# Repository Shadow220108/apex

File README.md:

<h1 align="center">
  <br>

  <br>
  Apex
  <br>
</h1>
<h3 align="center">
A fully open-sourced compact devboard inspired by the Seed Studio Xiao RP2040 with extra features such as LiPo support 
</h3>

| Front Render | Back Render | 
| --- | --- |
|  |  | 

| Zine |
| --- |
|  |

## Features
- **RP2040 MCU** - Dual ARM Cortex-M0+ @ 133MHz MCU.
- **Very compact, XIAO SEEED inspired formfactor**.
- **4 ADC and 7 digital GPIO pins**.
- **5V and 3.3V power pins**.
- Power indicator LED, addressable LED and another RGB LED
- LiPo Battery support and charging circuit
- **USB C** - for programming and power.

## PCB Design 
| .jpg) |
|--- |  

 ### The PCB is 4 layers with dimensions 21x17.8mm, made to be easily replacable to any Xiao board.  

 ### All the PCB files are [here](https://github.com/Shadow220108/apex/blob/main/PCB) 

| Front Layer | Inner Layer 1 |
| --- | --- |
| .jpg) | .jpg) |
| Inner Layer 2 | Bottom layer |
| .jpg) | .jpg) |

## Schematics  

Here are the schematic designs,

|  |
| --- |  

## Pinout  

This is a general pinout 

|  | 
| --- | 

( Credits to the Seed Studio for making this, since my board is inspired on the Xiao, I have used the pinout provided by them ) 

## Why was it made?  

While using the Seed Studio Xiao RP2040 for one of my projects, I realised it doesn't have LiPo support   
and I couldn't use it, unfortunately I had to use a different MCU then, but now I designed one with  
the simplicity of RP2040 with being able to charge LiPo 

## How you can get one for yourself? 

That is pretty easy, you have all the files you will need in the production folder, order the development  
board from any PCB fab ( I chose JLC cause its cheap and has good quality ) and BINGO! You will have it  
to use for any purpose you want!  

## How do you use it?  
You can use it as any normal RP2040 Devboard, enter the boootloader mode  
by holding the BOOT buttom while connecting to your device, flash it with  
firmware and you are good to go!  I have attached a simple code to blink the LED  
available on the board.  

## BOM  
|Name|Purpose          |Quantity|Total Cost (USD)|Link               |Distributor|
|----|-----------------|--------|----------------|-------------------|-----------|
|PCBA|Development Board|2       |79.03           |https://jlcpcb.com/|JLCPCB     |
| | | Total | 79.03 | 

LCSC BOM for the components on board is [here](https://github.com/Shadow220108/apex/blob/main/production/apex_bom.csv)

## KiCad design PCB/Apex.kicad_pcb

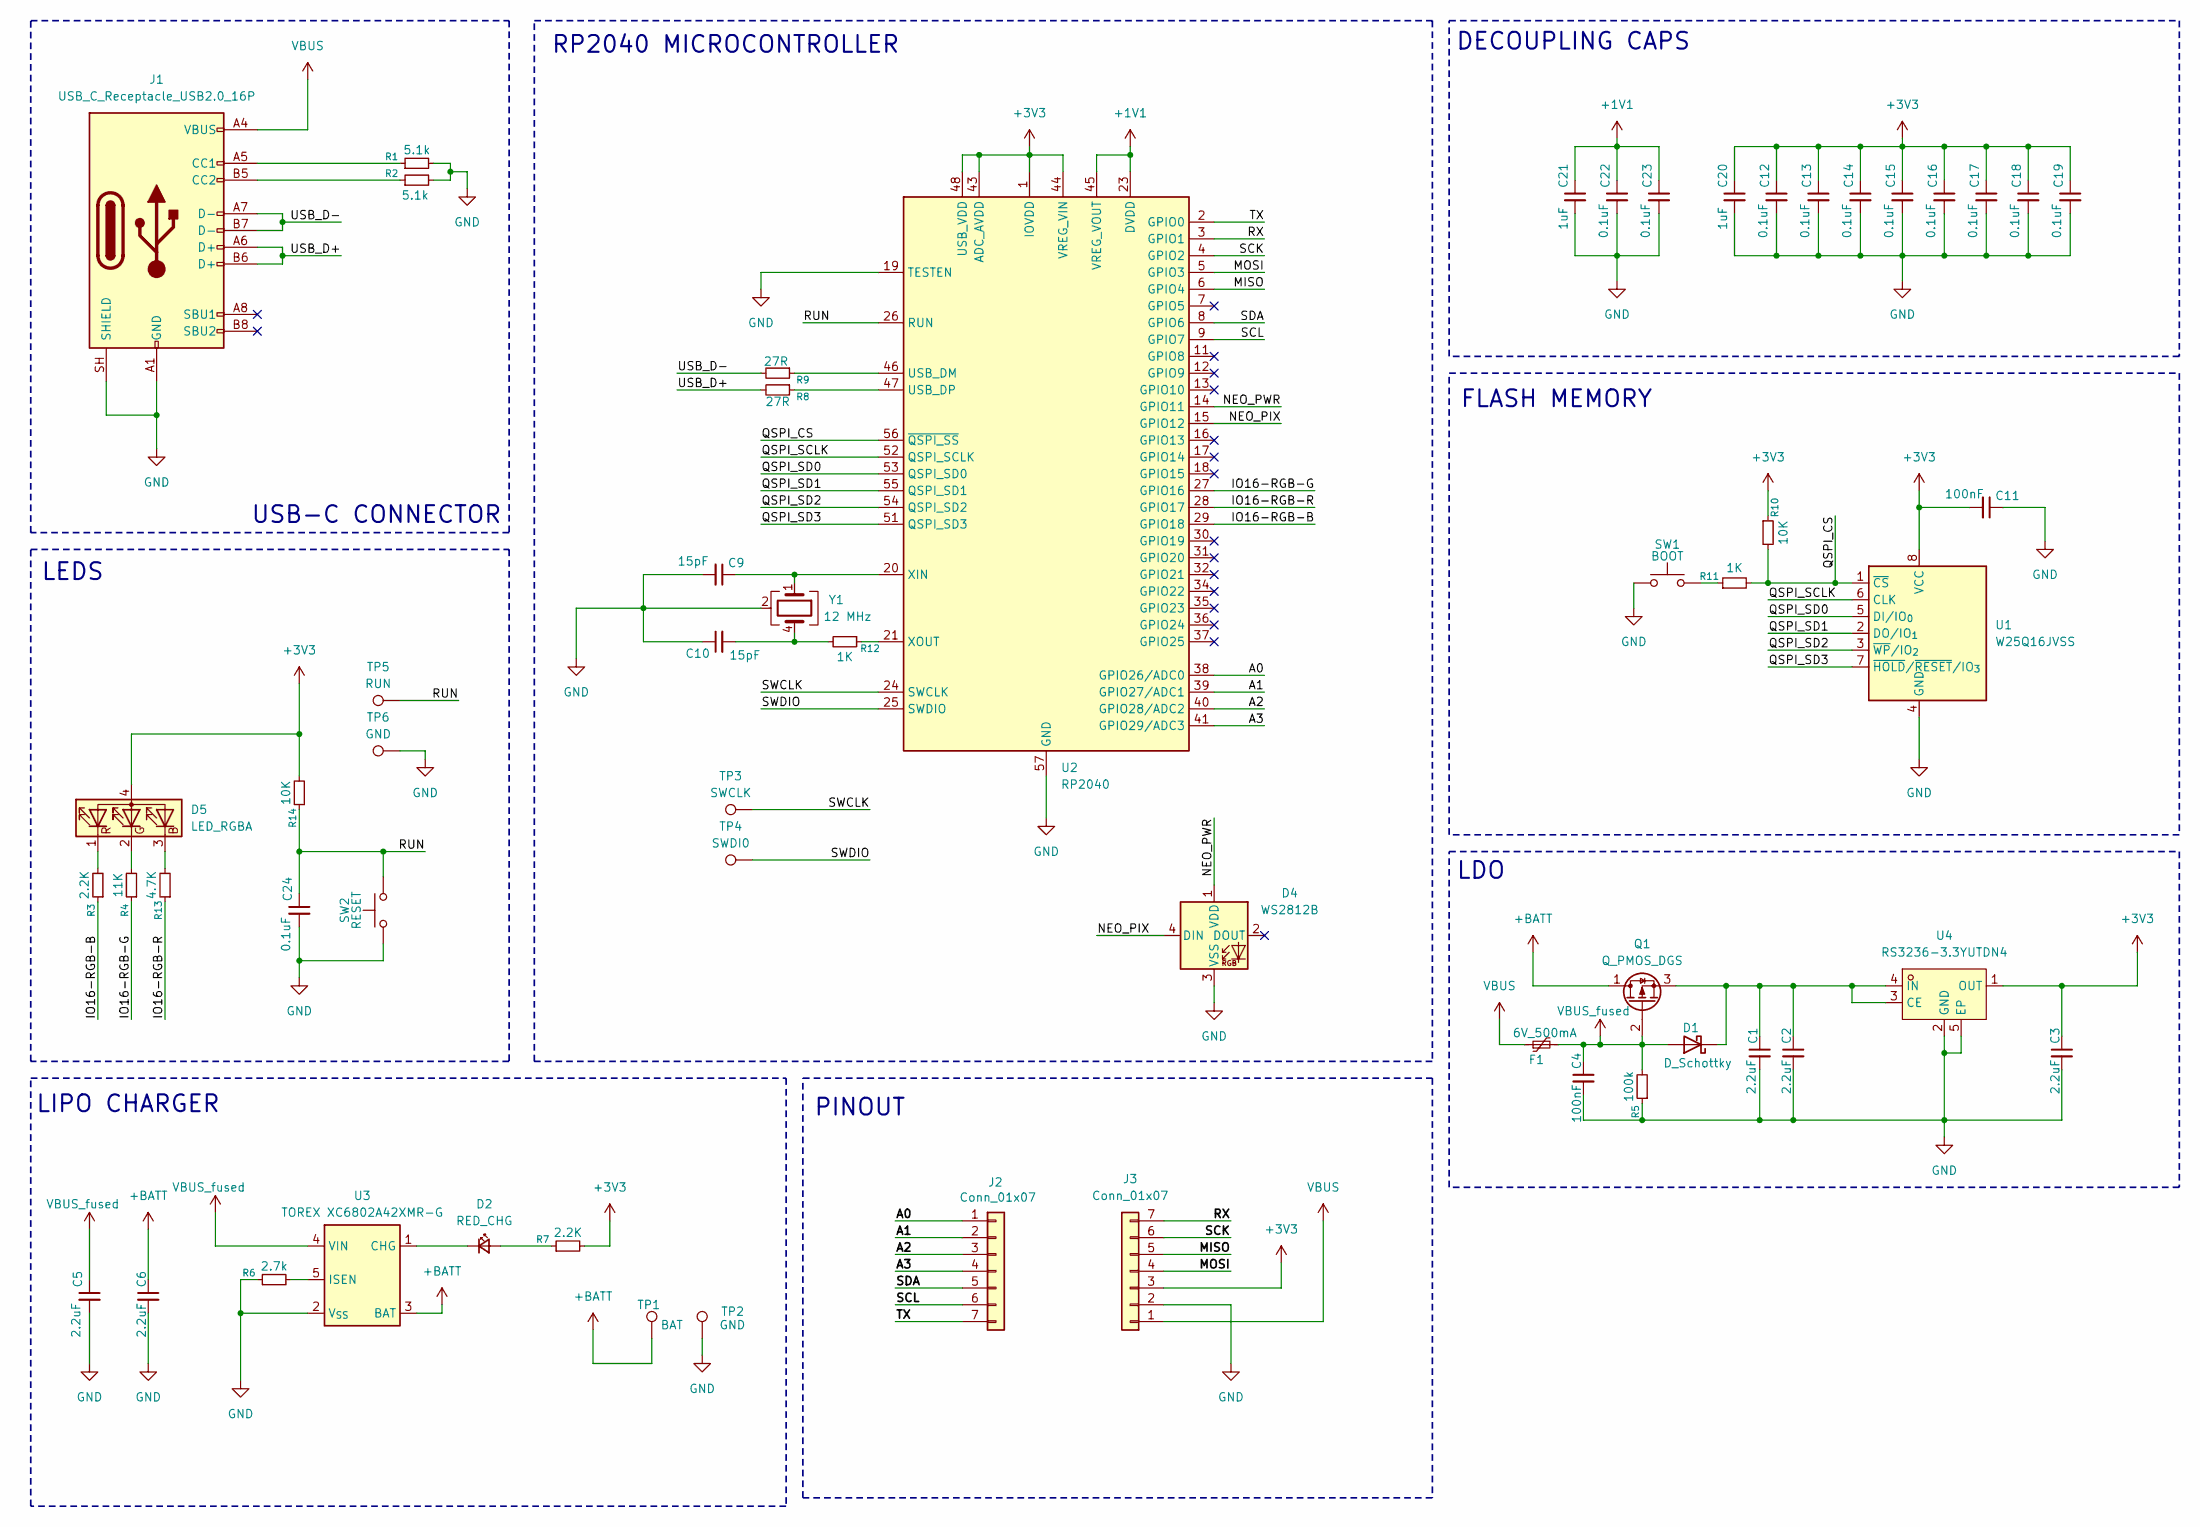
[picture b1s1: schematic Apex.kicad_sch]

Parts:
C1, C2, C3, C5, C6: 2.2uF; C_0201_0603Metric
C4, C11: 100nF; C_0201_0603Metric
C9, C10: 15pF; C_0201_0603Metric
C12, C13, C14, C15, C16, C17, C18, C19, C22, C23, C24: 0.1uF; C_0201_0603Metric
C20, C21: 1uF; C_0201_0603Metric
D1: D_Schottky; D_SOD-523
D2: RED_CHG; LED_0603_1608Metric
D4: WS2812B; LED_SK6805_PLCC4_2.4x2.7mm_P1.3mm
D5: LED_RGBA; LED_SK6812_EC15_1.5x1.5mm
F1: 6V_500mA; Fuse_0402_1005Metric
J1: USB_C_Receptacle_USB2.0_16P; USB-C_SMD-TYPE-C-31-M-12_1
J2, J3: Conn_01x07; PinHeader_1x07_P2.54mm_Vertical
Q1: Q_PMOS_DGS; SOT-323_SC-70
R1, R2: 5.1k; R_0201_0603Metric
R3, R7: 2.2K; R_0201_0603Metric
R4: 11K; R_0201_0603Metric
R5: 100k; R_0201_0603Metric
R6: 2.7k; R_0201_0603Metric
R8, R9: 27R; R_0201_0603Metric
R10, R14: 10K; R_0201_0603Metric
R11, R12: 1K; R_0201_0603Metric
R13: 4.7K; R_0201_0603Metric
SW1: BOOT; KEY-SMD_L3.0-W2.5-LS4.0_TD-1183SN
SW2: RESET; KEY-SMD_L3.0-W2.5-LS4.0_TD-1183SN
TP1: BAT; TestPoint_Pad_D1.0mm
TP2, TP6: GND; TestPoint_Pad_D1.0mm
TP3: SWCLK; TestPoint_Pad_D1.0mm
TP4: SWDI0; TestPoint_Pad_D1.0mm
TP5: RUN; TestPoint_Pad_D1.0mm
U1: W25Q16JVSS; USON-8_L3.0-W2.0-P0.50-BL-EP-1
U2: RP2040; QFN-56-1EP_7x7mm_P0.4mm_EP3.2x3.2mm
U3: TOREX XC6802A42XMR-G; SOT-23-5
U4: RS3236-3.3YUTDN4; XDFN-4_L1.0-W1.0-P0.65-BL-EP; MPN RS3236-3.3YUTDN4; LCSC Part C379350
Y1: 12 MHz; Crystal_SMD_1210-4Pin_1.2x1.0mm

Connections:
+1V1: C21.1, C22.1, C23.1, U2.23 (DVDD), U2.45 (VREG_VOUT), U2.50 (DVDD)
+3V3: C3.1, C11.2, C12.1, C13.1, C14.1, C15.1, C16.1, C17.1, C18.1, C19.1, C20.1, D5.4 (A), J3.3, R7.2, R10.1, R14.2, U1.8 (VCC), U2.1 (IOVDD), U2.10 (IOVDD), U2.22 (IOVDD), U2.33 (IOVDD), U2.42 (IOVDD), U2.43 (ADC_AVDD), U2.44 (VREG_VIN), U2.48 (USB_VDD), U2.49 (IOVDD), U4.1 (OUT)
+BATT: C6.1, Q1.1 (D), TP1.1 (1_1), U3.3 (BAT)
/A0: J2.1, U2.38 (GPIO26/ADC0)
/A1: J2.2, U2.39 (GPIO27/ADC1)
/A2: J2.3, U2.40 (GPIO28/ADC2)
/A3: J2.4, U2.41 (GPIO29/ADC3)
/IO16-RGB-B: R3.1, U2.29 (GPIO18)
/IO16-RGB-G: R4.1, U2.27 (GPIO16)
/IO16-RGB-R: R13.1, U2.28 (GPIO17)
/MISO: J3.5, U2.6 (GPIO4)
/MOSI: J3.4, U2.5 (GPIO3)
/NEO_PIX: D4.4 (DIN), U2.15 (GPIO12)
/NEO_PWR: D4.1 (VDD), U2.14 (GPIO11)
/QSPI_CS: R10.2, R11.2, U1.1 (~CS), U2.56 (~QSPI_SS)
/QSPI_SCLK: U1.6 (CLK), U2.52 (QSPI_SCLK)
/QSPI_SD0: U1.5 (DI/IO_{0}), U2.53 (QSPI_SD0)
/QSPI_SD1: U1.2 (DO/IO_{1}), U2.55 (QSPI_SD1)
/QSPI_SD2: U1.3 (~WP/IO_{2}), U2.54 (QSPI_SD2)
/QSPI_SD3: U1.7 (~HOLD/~RESET/IO_{3}), U2.51 (QSPI_SD3)
/RUN: C24.1, R14.1, SW2.2, TP5.1 (1_1), U2.26 (RUN)
/RX: J3.7, U2.3 (GPIO1)
/SCK: J3.6, U2.4 (GPIO2)
/SCL: J2.6, U2.9 (GPIO7)
/SDA: J2.5, U2.8 (GPIO6)
/SWCLK: TP3.1 (1_1), U2.24 (SWCLK)
/SWDIO: TP4.1 (1_1), U2.25 (SWDIO)
/TX: J2.7, U2.2 (GPIO0)
/USB_D+: J1.A6 (D+), J1.B6 (D+), R8.2
/USB_D-: J1.A7 (D-), J1.B7 (D-), R9.2
GND: C1.2, C2.2, C3.2, C4.2, C5.2, C6.2, C9.2, C10.1, C11.1, C12.2, C13.2, C14.2, C15.2, C16.2, C17.2, C18.2, C19.2, C20.2, C21.2, C22.2, C23.2, C24.2, D4.3 (VSS), J1.A1 (GND), J1.A12 (GND), J1.B1 (GND), J1.B12 (GND), J1.SH (SHIELD), J3.2, R1.2, R2.2, R5.1, R6.1, SW1.1, SW2.1, TP2.1 (1_1), TP6.1 (1_1), U1.4 (GND), U2.19 (TESTEN), U2.57 (GND), U3.2 (V_{SS}), U4.2 (GND), U4.5 (EP), Y1.2 (G), Y1.3 (G)
unnamed: C10.2, R12.2, Y1.4
unnamed: C1.1, C2.1, D1.1 (K), Q1.3 (S), U4.3 (CE), U4.4 (IN)
unnamed: D2.2 (A), R7.1
unnamed: D2.1 (K), U3.1 (CHG)
unnamed: D5.3 (BK), R13.2
unnamed: D5.2 (GK), R4.2
unnamed: D5.1 (RK), R3.2
unnamed: J1.A5 (CC1), R1.1
unnamed: J1.B5 (CC2), R2.1
unnamed: R11.1, SW1.2
unnamed: R9.1, U2.46 (USB_DM)
unnamed: R8.1, U2.47 (USB_DP)
unnamed: C9.1, U2.20 (XIN), Y1.1
unnamed: R12.1, U2.21 (XOUT)
unnamed: R6.2, U3.5 (ISEN)
VBUS: F1.1, J1.A4 (VBUS), J1.A9 (VBUS), J1.B4 (VBUS), J1.B9 (VBUS), J3.1
VBUS_fused: C4.1, C5.1, D1.2 (A), F1.2, Q1.2 (G), R5.2, U3.4 (VIN)

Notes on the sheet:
FLASH MEMORY
LEDS
USB-C CONNECTOR
LIPO CHARGER
LDO
PINOUT
RP2040 MICROCONTROLLER
DECOUPLING CAPS

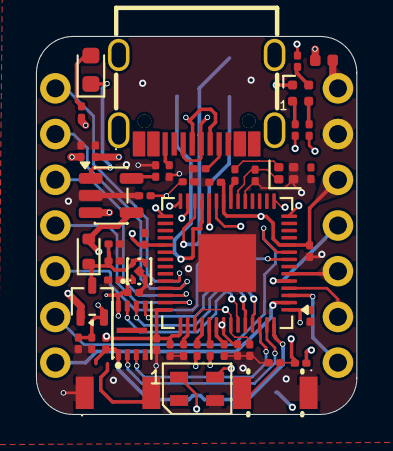
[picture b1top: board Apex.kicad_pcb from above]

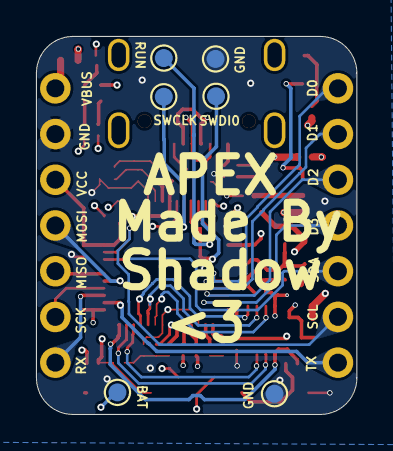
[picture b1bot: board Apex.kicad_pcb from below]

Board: 4 copper layers, 17.8 x 21.0 mm, 57 parts (8 on the bottom side), 47 nets.

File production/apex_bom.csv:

Designator,Footprint,Quantity,Value,LCSC Part #
"C1, C2, C3, C5, C6",0201,5,2.2uF,
"C10, C9",0201,2,15pF,
"C11, C4",0201,2,100nF,
"C12, C13, C14, C15, C16, C17, C18, C19, C22, C23, C24",0201,11,0.1uF,
"C20, C21",0201,2,1uF,
D1,D_SOD-523,1,D_Schottky,
D2,0603,1,RED_CHG,
D4,LED_SK6805_PLCC4_2.4x2.7mm_P1.3mm,1,WS2812B,
D5,LED_SK6812_EC15_1.5x1.5mm,1,LED_RGBA,
F1,0402,1,6V_500mA,
J1,USB-C_SMD-TYPE-C-31-M-12_1,1,USB_C_Receptacle_USB2.0_16P,C165948
"J2, J3",PinHeader_1x07_P2.54mm_Vertical,2,Conn_01x07,
Q1,SOT-323_SC-70,1,Q_PMOS_DGS,
"R1, R2",0201,2,5.1k,
"R10, R14",0201,2,10K,
R12,0201,1,1K,
R13,0201,1,4.7K,
"R3, R7",0201,2,2.2K,
R4,0201,1,11K,
R5,0201,1,100k,
R6,0201,1,2.7k,
"R8, R9",0201,2,27R,
SW1,KEY-SMD_L3.0-W2.5-LS4.0_TD-1183SN,1,BOOT,C2905192
SW2,KEY-SMD_L3.0-W2.5-LS4.0_TD-1183SN,1,RESET,C2905192
TP1,TestPoint_Pad_D1.0mm,1,BAT,
"TP2, TP6",TestPoint_Pad_D1.0mm,2,GND,
TP3,TestPoint_Pad_D1.0mm,1,SWCLK,
TP4,TestPoint_Pad_D1.0mm,1,SWDI0,
TP5,TestPoint_Pad_D1.0mm,1,RUN,
U1,USON-8_L3.0-W2.0-P0.50-BL-EP-1,1,W25Q16JVSS,C2973793
U2,QFN-56-1EP_7x7mm_P0.4mm_EP3.2x3.2mm,1,RP2040,
U3,SOT-23-5,1,TOREX XC6802A42XMR-G,
U4,XDFN-4_L1.0-W1.0-P0.65-BL-EP,1,RS3236-3.3YUTDN4,C379350
Y1,Crystal_SMD_1210-4Pin_1.2x1.0mm,1,12 MHz,

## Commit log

2026-06-20 adding some images
2026-06-20 adding bom
2026-06-20 adding zine and pinout
2026-06-20 adding zine and pinout and readme
